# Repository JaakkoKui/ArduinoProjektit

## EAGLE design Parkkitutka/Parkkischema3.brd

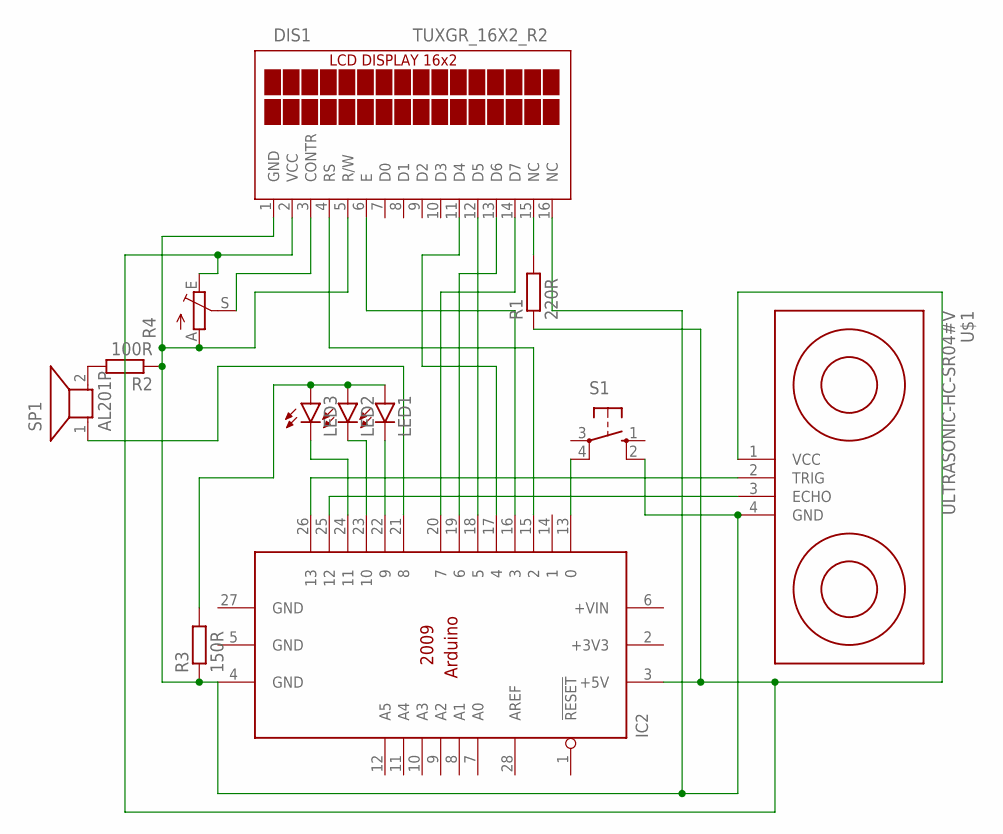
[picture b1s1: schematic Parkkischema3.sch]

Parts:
DIS1: TUXGR_16X2_R2
IC2: ARDUINO2009_10; ARDUINO2009
LED1, LED2, LED3: LED5MM
R1: 220R; 0204/7
R2: 100R; 0204/7
R3: 150R; 0204/7
R4: TRIM_EU-CA6V; CA6V
S1: 10-XX; B3F-10XX
SP1: AL201P
U$1: ULTRASONIC-HC-SR04#V

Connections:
+3V3: IC2.2 (+3V3)
GND: IC2.5 (GND), IC2.27 (GND)
unnamed: R2.2, SP1.2
unnamed: DIS1.4 (RS), IC2.15 (2)
unnamed: IC2.21 (8), SP1.1
unnamed: LED1.A, LED2.A, LED3.A, R3.2
unnamed: IC2.22 (9), LED1.K (C)
unnamed: DIS1.6 (E), IC2.16 (3)
unnamed: DIS1.3 (CONTR), R4.S
unnamed: DIS1.15 (NC), R1.2
unnamed: IC2.23 (10), LED2.K (C)
unnamed: IC2.24 (11), LED3.K (C)
unnamed: IC2.26 (13), U$1.2 (TRIG)
unnamed: IC2.13 (0), S1.4 (P1)
unnamed: DIS1.2 (VCC), IC2.3 (+5V), R1.1, R4.E, U$1.1 (VCC)
unnamed: DIS1.1 (GND), DIS1.5 (R/W), DIS1.16 (NC), IC2.4 (GND), R2.1, R3.1, R4.A, S1.2 (S1), U$1.4 (GND)
unnamed: DIS1.11 (D4), IC2.17 (4)
unnamed: DIS1.12 (D5), IC2.18 (5)
unnamed: DIS1.13 (D6), IC2.19 (6)
unnamed: DIS1.14 (D7), IC2.20 (7)
unnamed: IC2.25 (12), U$1.3 (ECHO)

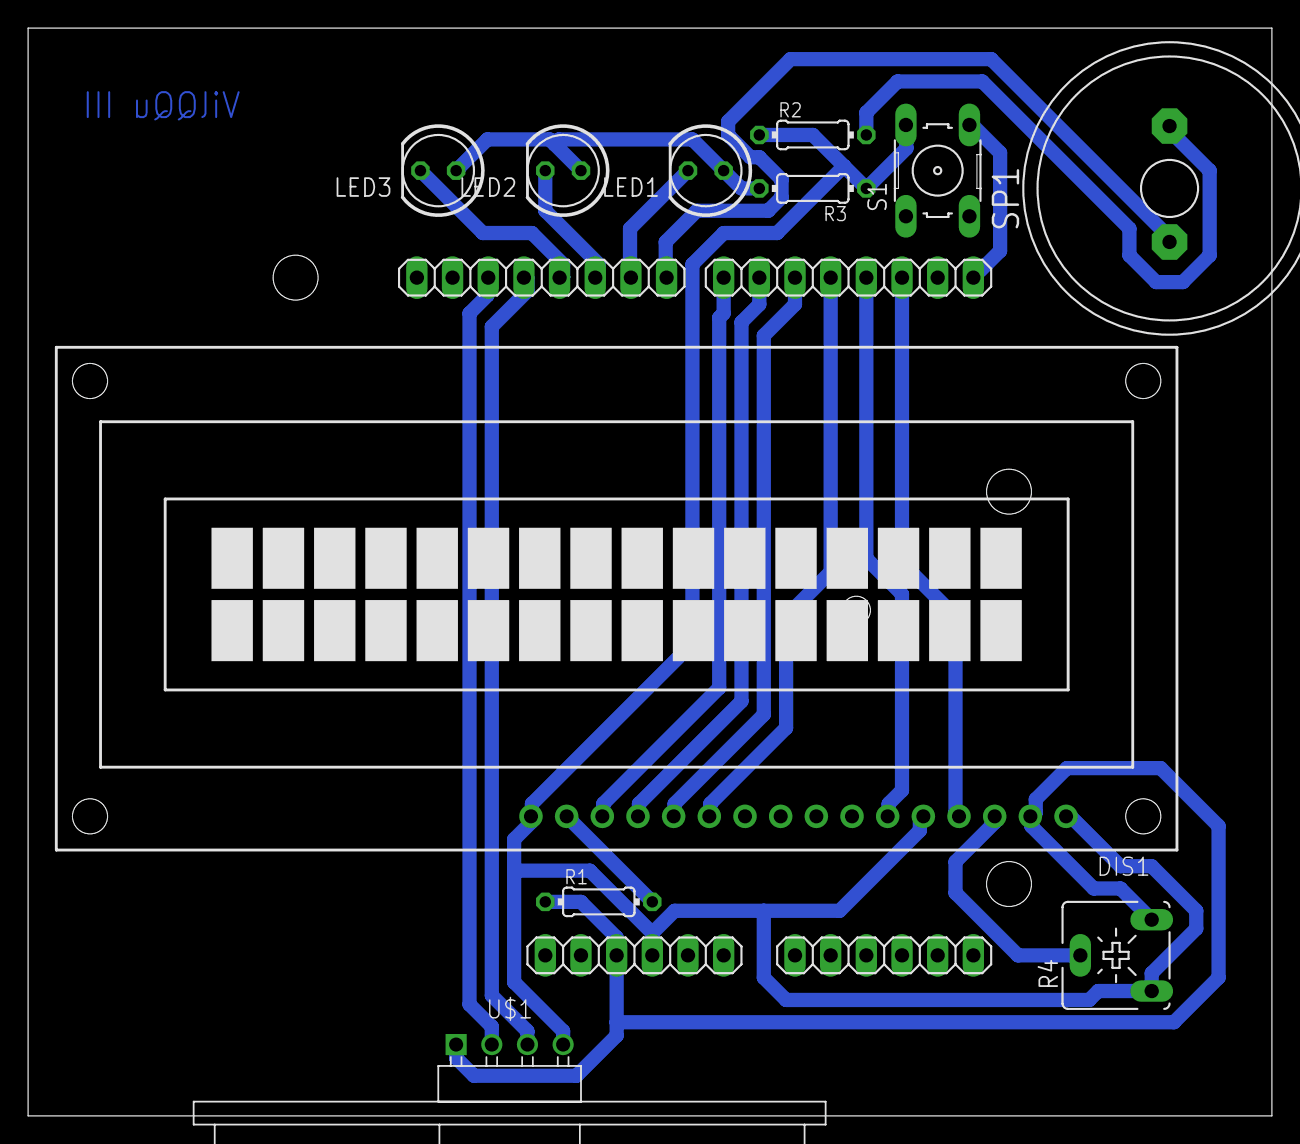
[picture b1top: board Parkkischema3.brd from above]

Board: 2 copper layers, 88.6 x 77.5 mm, 12 parts (0 on the bottom side), 20 nets.

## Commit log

2019-12-18 Add files via upload
    Parkkitutkan schema, boardi, koodi ja dokumentti

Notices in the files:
parts and their libraries:
diy-modules: Released under the Creative Commons Attribution 4.0 International License: http://creativecommons.org/licenses/by/4.0
